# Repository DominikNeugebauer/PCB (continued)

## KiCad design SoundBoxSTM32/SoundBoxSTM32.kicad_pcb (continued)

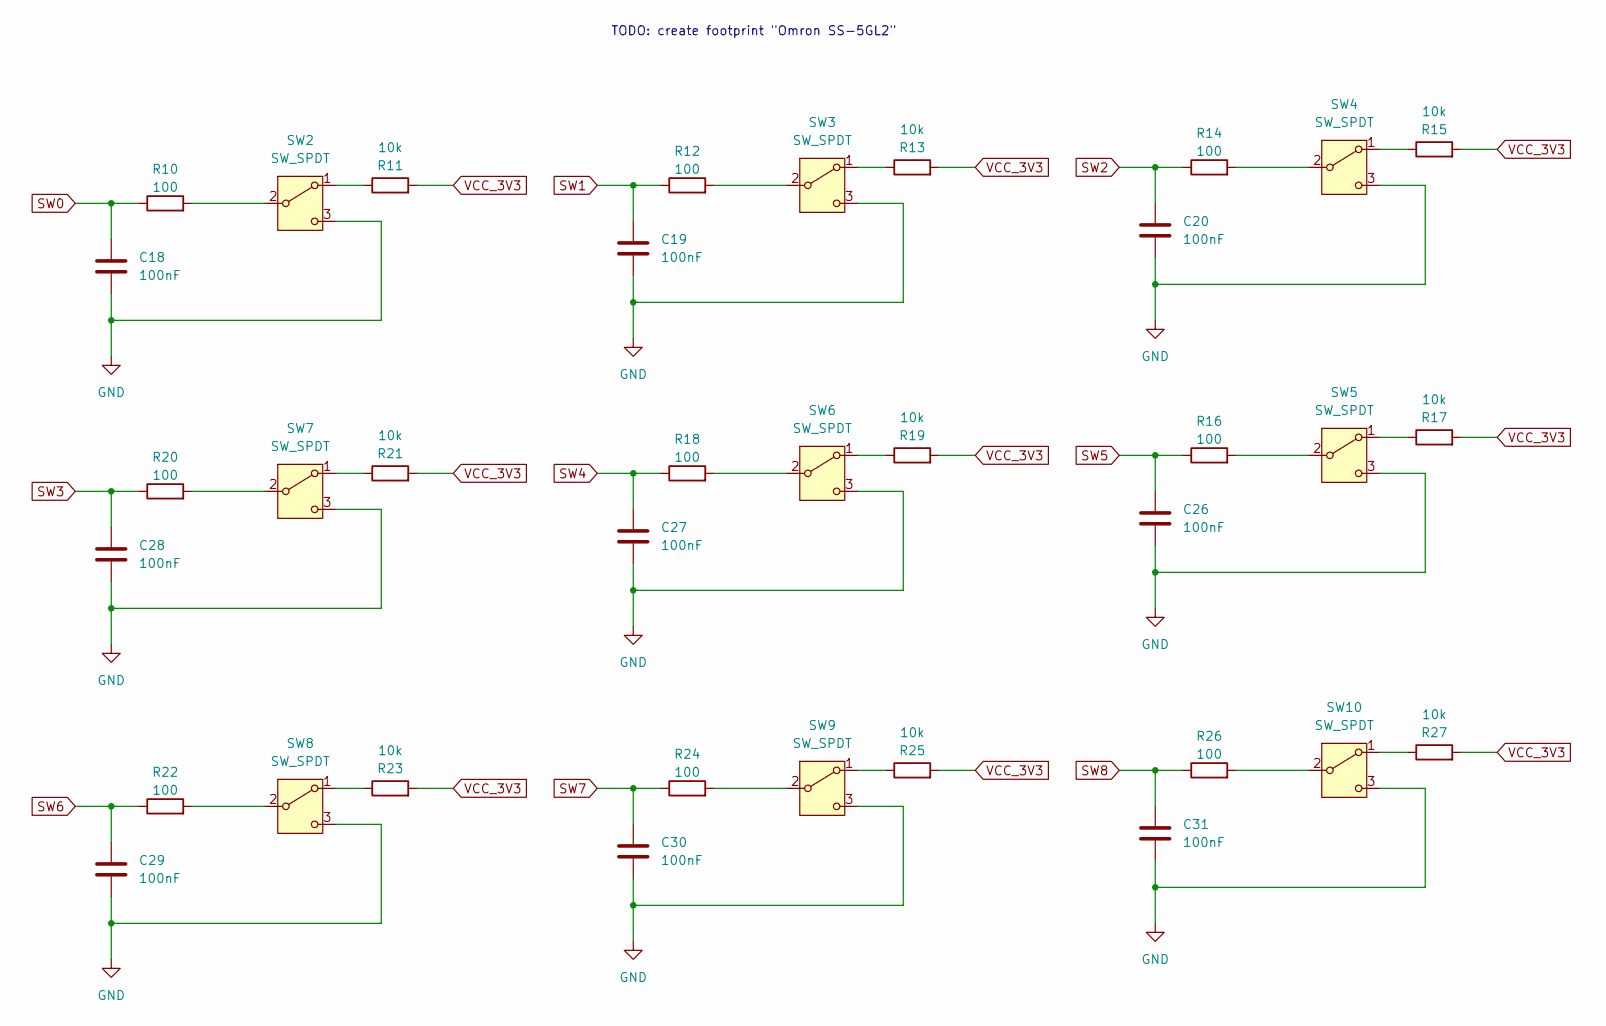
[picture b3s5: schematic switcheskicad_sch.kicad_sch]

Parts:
C18, C19, C20, C26, C27, C28, C29, C30, C31: 100nF; C_0603_1608Metric
R10, R12, R14, R16, R18, R20, R22, R24, R26: 100; R_0603_1608Metric
R11, R13, R15, R17, R19, R21, R23, R25, R27: 10k; R_0603_1608Metric
SW2, SW3, SW4, SW5, SW6, SW7, SW8, SW9, SW10: SW_SPDT; D2F-01L_OMR

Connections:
GND: C18.2, C19.2, C20.2, C26.2, C27.2, C28.2, C29.2, C30.2, C31.2, SW2.3 (C), SW3.3 (C), SW4.3 (C), SW5.3 (C), SW6.3 (C), SW7.3 (C), SW8.3 (C), SW9.3 (C), SW10.3 (C); also elsewhere on the board
unnamed: R11.1, SW2.1 (A)
unnamed: R10.2, SW2.2 (B)
unnamed: R13.1, SW3.1 (A)
unnamed: R12.2, SW3.2 (B)
unnamed: R15.1, SW4.1 (A)
unnamed: R14.2, SW4.2 (B)
unnamed: R17.1, SW5.1 (A)
unnamed: R16.2, SW5.2 (B)
unnamed: R19.1, SW6.1 (A)
unnamed: R18.2, SW6.2 (B)
unnamed: R21.1, SW7.1 (A)
unnamed: R20.2, SW7.2 (B)
unnamed: R23.1, SW8.1 (A)
unnamed: R22.2, SW8.2 (B)
unnamed: R25.1, SW9.1 (A)
unnamed: R24.2, SW9.2 (B)
unnamed: R27.1, SW10.1 (A)
unnamed: R26.2, SW10.2 (B)
SW0: C18.1, R10.1; also elsewhere on the board
SW1: C19.1, R12.1; also elsewhere on the board
SW2: C20.1, R14.1; also elsewhere on the board
SW3: C28.1, R20.1; also elsewhere on the board
SW4: C27.1, R18.1; also elsewhere on the board
SW5: C26.1, R16.1; also elsewhere on the board
SW6: C29.1, R22.1; also elsewhere on the board
SW7: C30.1, R24.1; also elsewhere on the board
SW8: C31.1, R26.1; also elsewhere on the board
VCC_3V3: R11.2, R13.2, R15.2, R17.2, R19.2, R21.2, R23.2, R25.2, R27.2; also elsewhere on the board

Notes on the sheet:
TODO: create footprint "Omron SS-5GL2"

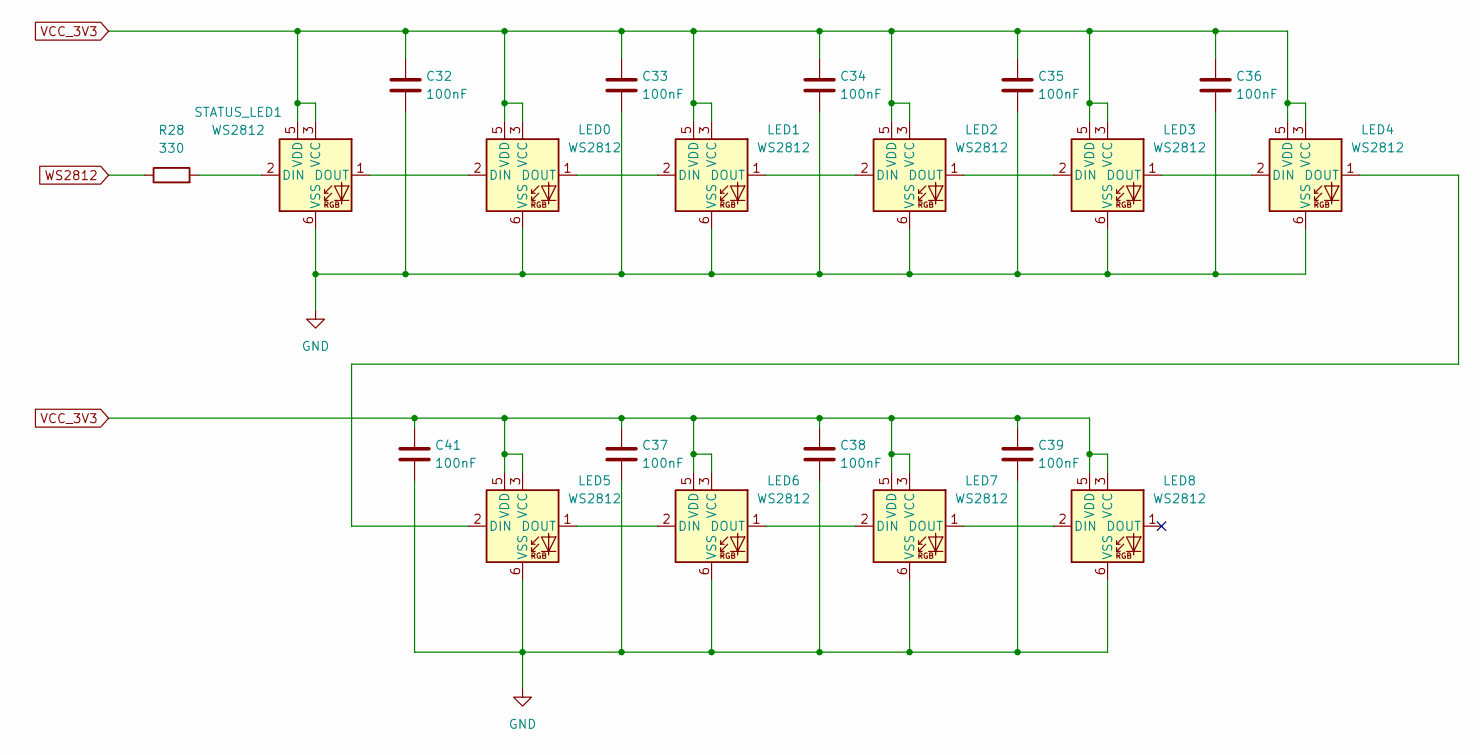
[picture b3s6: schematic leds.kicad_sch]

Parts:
C32, C33, C34, C35, C36, C37, C38, C39, C41: 100nF; C_0603_1608Metric
LED0, LED1, LED2, LED3, LED4, LED5, LED6, LED7, LED8: WS2812; LED_WS2812_PLCC6_5.0x5.0mm_P1.6mm
R28: 330; R_0603_1608Metric
STATUS_LED1: WS2812; LED_WS2812_PLCC6_5.0x5.0mm_P1.6mm

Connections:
GND: C32.2, C33.2, C34.2, C35.2, C36.2, C37.2, C38.2, C39.2, C41.2, LED0.6 (VSS), LED1.6 (VSS), LED2.6 (VSS), LED3.6 (VSS), LED4.6 (VSS), LED5.6 (VSS), LED6.6 (VSS), LED7.6 (VSS), LED8.6 (VSS), STATUS_LED1.6 (VSS); also elsewhere on the board
unnamed: LED0.2 (DIN), STATUS_LED1.1 (DOUT)
unnamed: LED0.1 (DOUT), LED1.2 (DIN)
unnamed: LED1.1 (DOUT), LED2.2 (DIN)
unnamed: LED2.1 (DOUT), LED3.2 (DIN)
unnamed: LED3.1 (DOUT), LED4.2 (DIN)
unnamed: LED4.1 (DOUT), LED5.2 (DIN)
unnamed: LED5.1 (DOUT), LED6.2 (DIN)
unnamed: LED6.1 (DOUT), LED7.2 (DIN)
unnamed: LED7.1 (DOUT), LED8.2 (DIN)
unnamed: R28.2, STATUS_LED1.2 (DIN)
VCC_3V3: C32.1, C33.1, C34.1, C35.1, C36.1, C37.1, C38.1, C39.1, C41.1, LED0.3 (VCC), LED0.5 (VDD), LED1.3 (VCC), LED1.5 (VDD), LED2.3 (VCC), LED2.5 (VDD), LED3.3 (VCC), LED3.5 (VDD), LED4.3 (VCC), LED4.5 (VDD), LED5.3 (VCC), LED5.5 (VDD), LED6.3 (VCC), LED6.5 (VDD), LED7.3 (VCC), LED7.5 (VDD), LED8.3 (VCC), LED8.5 (VDD), STATUS_LED1.3 (VCC), STATUS_LED1.5 (VDD); also elsewhere on the board
WS2812: R28.1; also elsewhere on the board

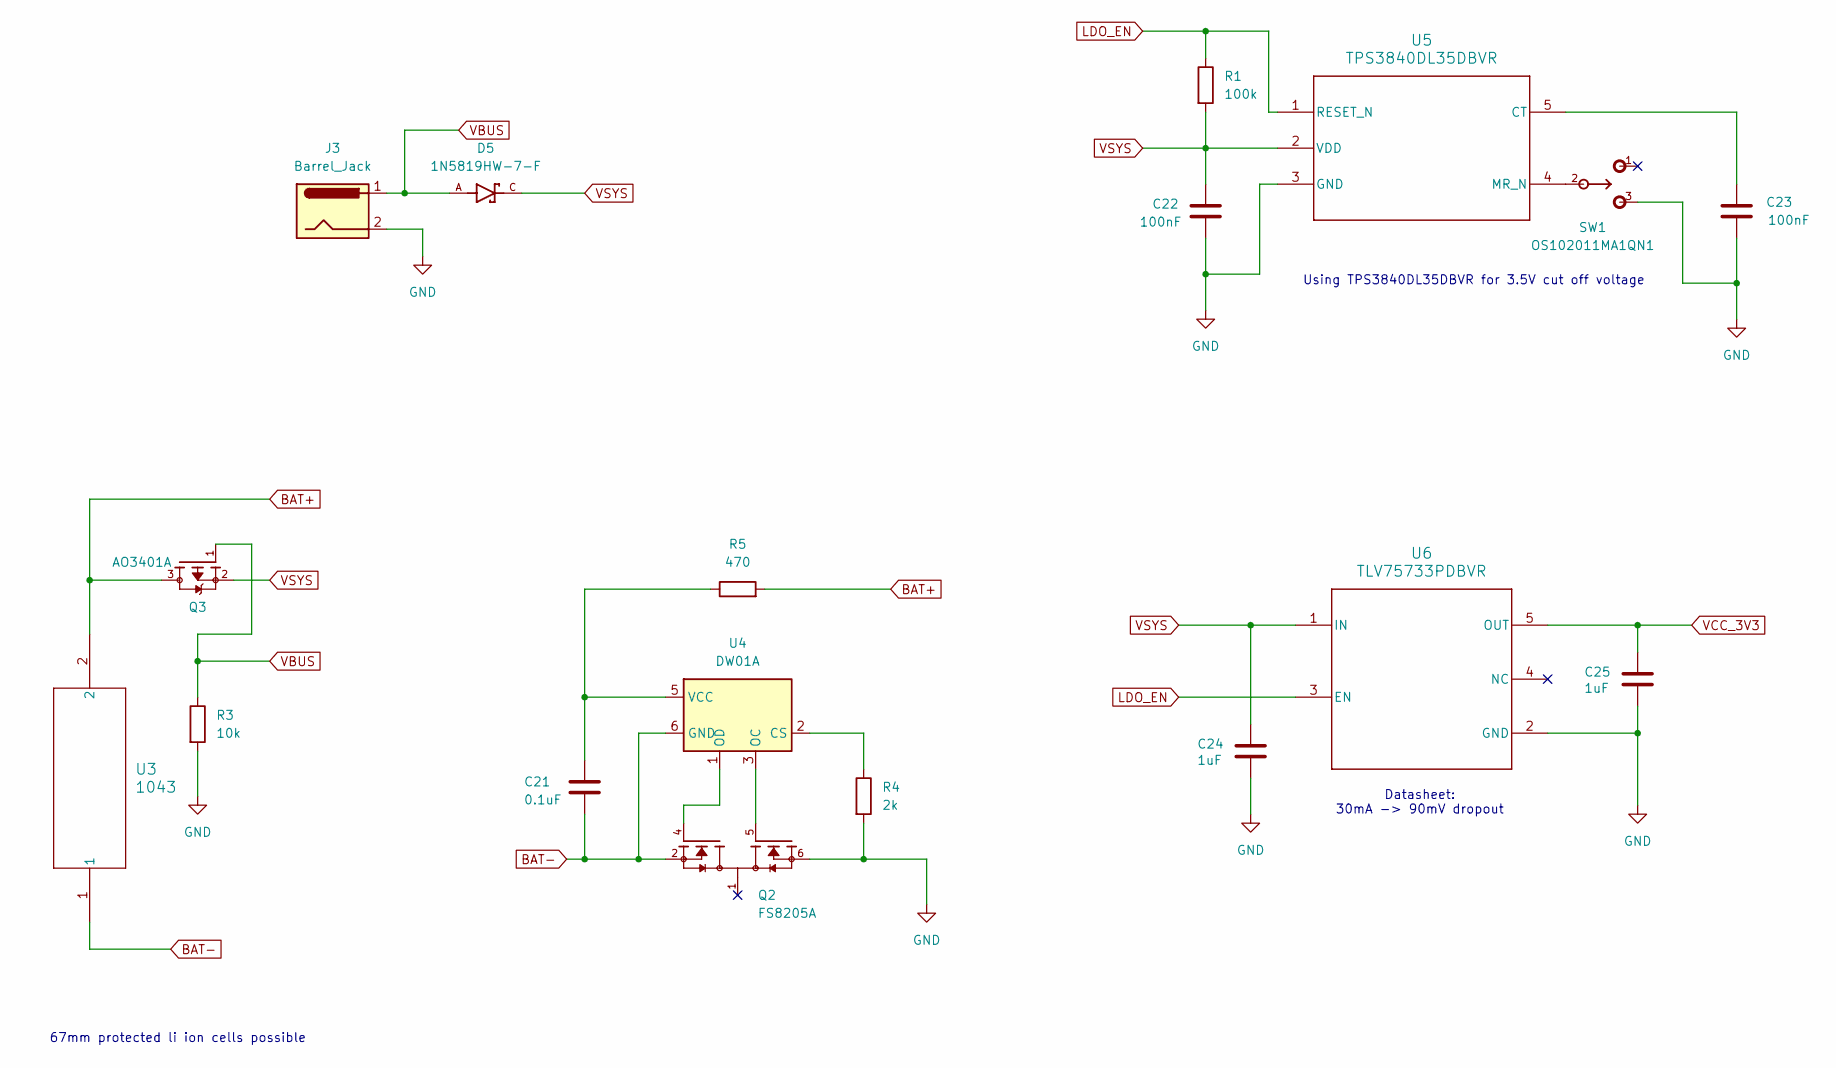
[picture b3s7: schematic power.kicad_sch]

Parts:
C21: 0.1uF; C_0603_1608Metric
C22, C23: 100nF; C_0603_1608Metric
C24, C25: 1uF; C_0603_1608Metric
D5: 1N5819HW-7-F; PARTREV 18-2
J3: Barrel_Jack; BarrelJack_Horizontal
Q2: FS8205A; PARTREV 1.7
Q3: AO3401A; PMOS-SOT23-3
R1: 100k; R_0603_1608Metric
R3: 10k; R_0603_1608Metric
R4: 2k; R_0603_1608Metric
R5: 470; R_0603_1608Metric
SW1: OS102011MA1QN1; MANUFACTURER_PART_NUMBER OS102011MA1QN1
U3: 1043; 1043_KEY
U4: DW01A; SOT-23-6
U5: TPS3840DL35DBVR; SOT-23-5
U6: TLV75733PDBVR; SOT95P280X145-5N_TLV75733PDBVR

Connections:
BAT+: Q3.3, R5.2, U3.2; also elsewhere on the board
BAT-: C21.2, Q2.2, Q2.3, U3.1, U4.6 (GND); also elsewhere on the board
GND: C22.2, C23.2, C24.2, C25.2, J3.2, Q2.6, Q2.7, R3.2, R4.2, SW1.3, U5.3 (GND), U6.2 (GND); also elsewhere on the board
LDO_EN: R1.1, U5.1 (RESET_N), U6.3 (EN)
unnamed: R4.1, U4.2 (CS)
unnamed: Q2.5, U4.3 (OC)
unnamed: Q2.4, U4.1 (OD)
unnamed: C21.1, R5.1, U4.5 (VCC)
unnamed: C23.1, U5.5 (CT)
unnamed: SW1.2, U5.4 (MR_N)
VBUS: D5.A, J3.1, Q3.1, R3.1
VCC_3V3: C25.1, U6.5 (OUT); also elsewhere on the board
VSYS: C22.1, C24.1, D5.C, Q3.2, R1.2, U5.2 (VDD), U6.1 (IN); also elsewhere on the board

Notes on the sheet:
Datasheet: 30mA -> 90mV dropout
67mm protected li ion cells possible
Using TPS3840DL35DBVR for 3.5V cut off voltage

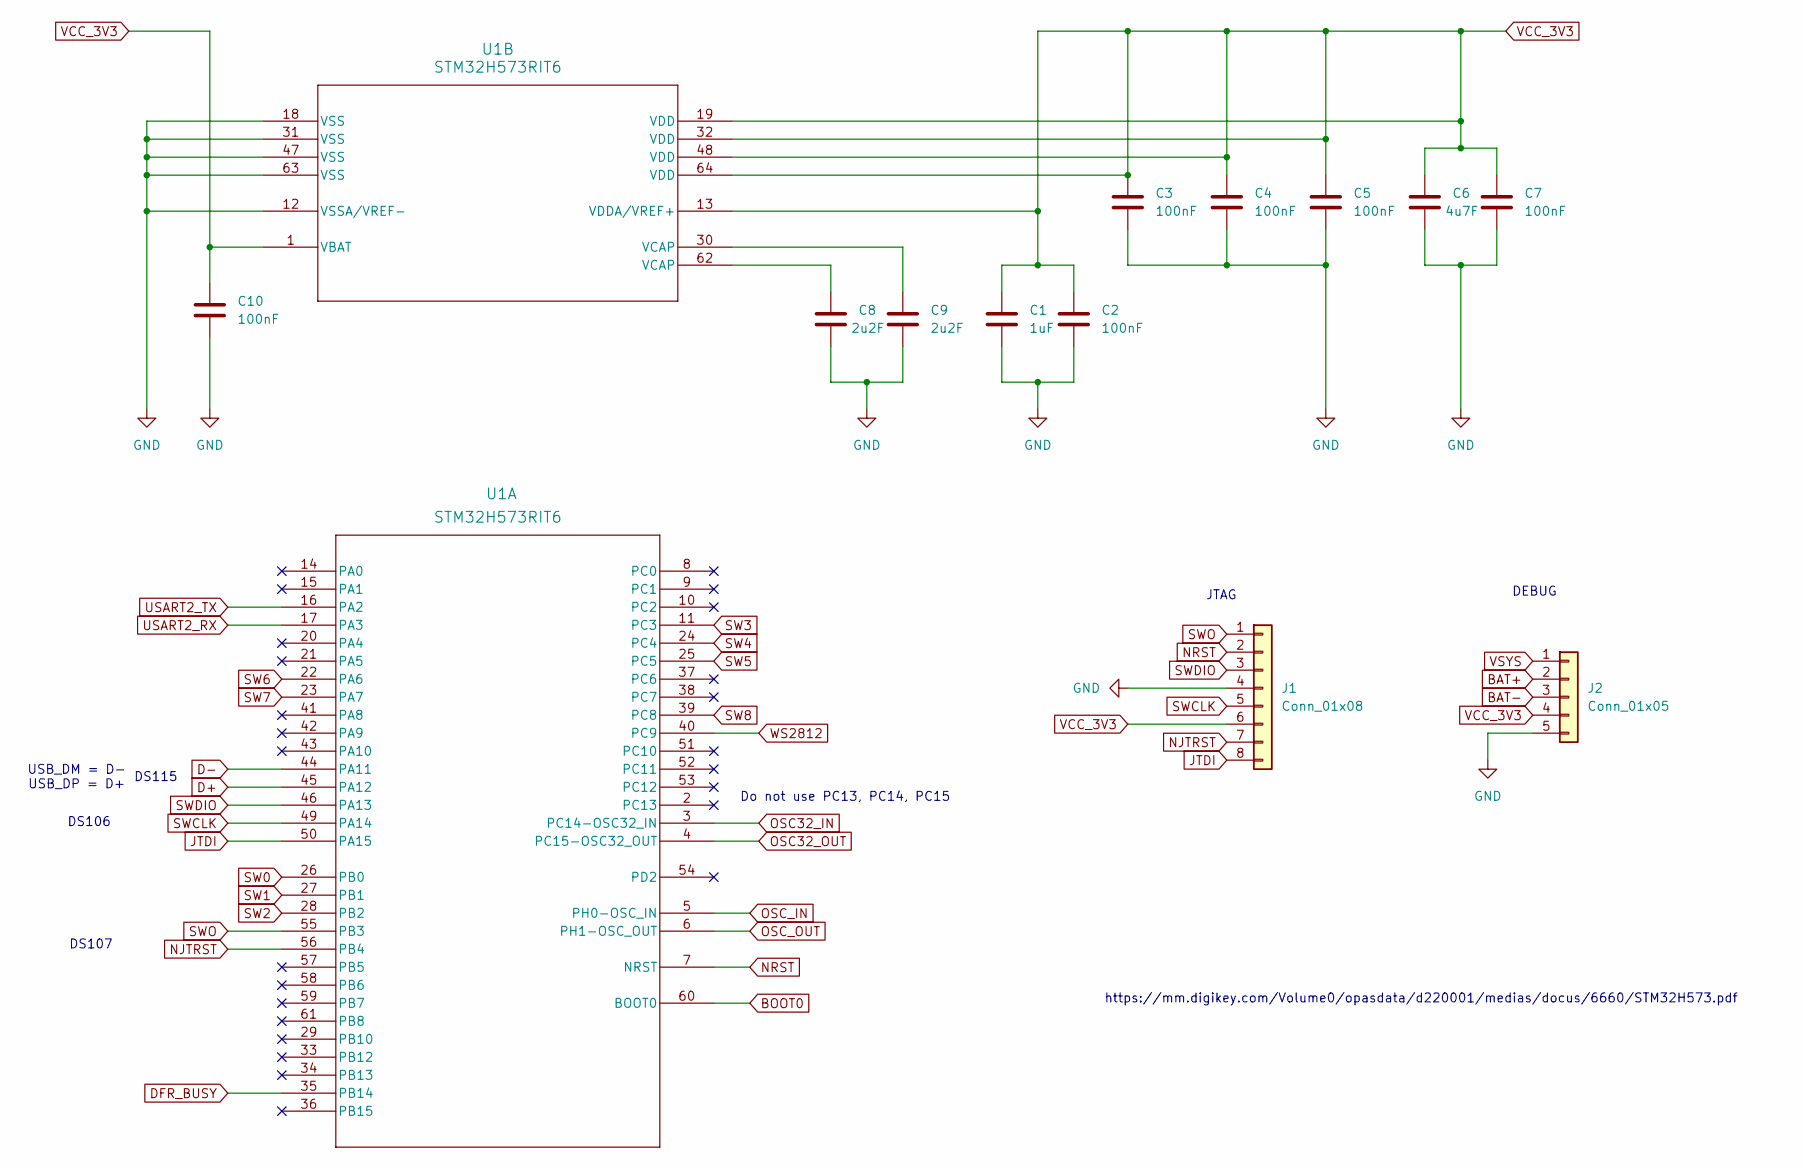
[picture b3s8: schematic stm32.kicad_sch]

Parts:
C1: 1uF; C_0603_1608Metric
C2, C3, C4, C5, C7, C10: 100nF; C_0603_1608Metric
C6: 4u7F; C_0603_1608Metric
C8, C9: 2u2F; C_0603_1608Metric
J1: Conn_01x08; PinHeader_1x08_P2.54mm_Vertical
J2: Conn_01x05; PinHeader_1x05_P2.54mm_Vertical
U1: STM32H573RIT6

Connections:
BAT+: J2.2; also elsewhere on the board
BAT-: J2.3; also elsewhere on the board
BOOT0: U1.60 (BOOT0); also elsewhere on the board
D+: U1.45 (PA12)
D-: U1.44 (PA11)
DFR_BUSY: U1.35 (PB14); also elsewhere on the board
GND: C1.2, C2.2, C3.2, C4.2, C5.2, C6.2, C7.2, C8.2, C9.2, C10.2, J1.4, J2.5, U1.12 (VSSA/VREF-), U1.18 (VSS), U1.31 (VSS), U1.47 (VSS), U1.63 (VSS); also elsewhere on the board
JTDI: J1.8, U1.50 (PA15)
NJTRST: J1.7, U1.56 (PB4)
NRST: J1.2, U1.7 (NRST); also elsewhere on the board
unnamed: C8.1, U1.62 (VCAP)
unnamed: C9.1, U1.30 (VCAP)
OSC32_IN: U1.3 (PC14-OSC32_IN); also elsewhere on the board
OSC32_OUT: U1.4 (PC15-OSC32_OUT); also elsewhere on the board
OSC_IN: U1.5 (PH0-OSC_IN); also elsewhere on the board
OSC_OUT: U1.6 (PH1-OSC_OUT); also elsewhere on the board
SW0: U1.26 (PB0); also elsewhere on the board
SW1: U1.27 (PB1); also elsewhere on the board
SW2: U1.28 (PB2); also elsewhere on the board
SW3: U1.11 (PC3); also elsewhere on the board
SW4: U1.24 (PC4); also elsewhere on the board
SW5: U1.25 (PC5); also elsewhere on the board
SW6: U1.22 (PA6); also elsewhere on the board
SW7: U1.23 (PA7); also elsewhere on the board
SW8: U1.39 (PC8); also elsewhere on the board
SWCLK: J1.5, U1.49 (PA14)
SWDIO: J1.3, U1.46 (PA13)
SWO: J1.1, U1.55 (PB3)
USART2_RX: U1.17 (PA3); also elsewhere on the board
USART2_TX: U1.16 (PA2); also elsewhere on the board
VCC_3V3: C1.1, C2.1, C3.1, C4.1, C5.1, C6.1, C7.1, C10.1, J1.6, J2.4, U1.1 (VBAT), U1.13 (VDDA/VREF+), U1.19 (VDD), U1.32 (VDD), U1.48 (VDD), U1.64 (VDD); also elsewhere on the board
VSYS: J2.1; also elsewhere on the board
WS2812: U1.40 (PC9); also elsewhere on the board

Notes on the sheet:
JTAG
DS106
https://mm.digikey.com/Volume0/opasdata/d220001/medias/docus/6660/STM32H573.pdf
DEBUG
Do not use PC13, PC14, PC15
DS115
DS107
USB_DM = D- USB_DP = D+

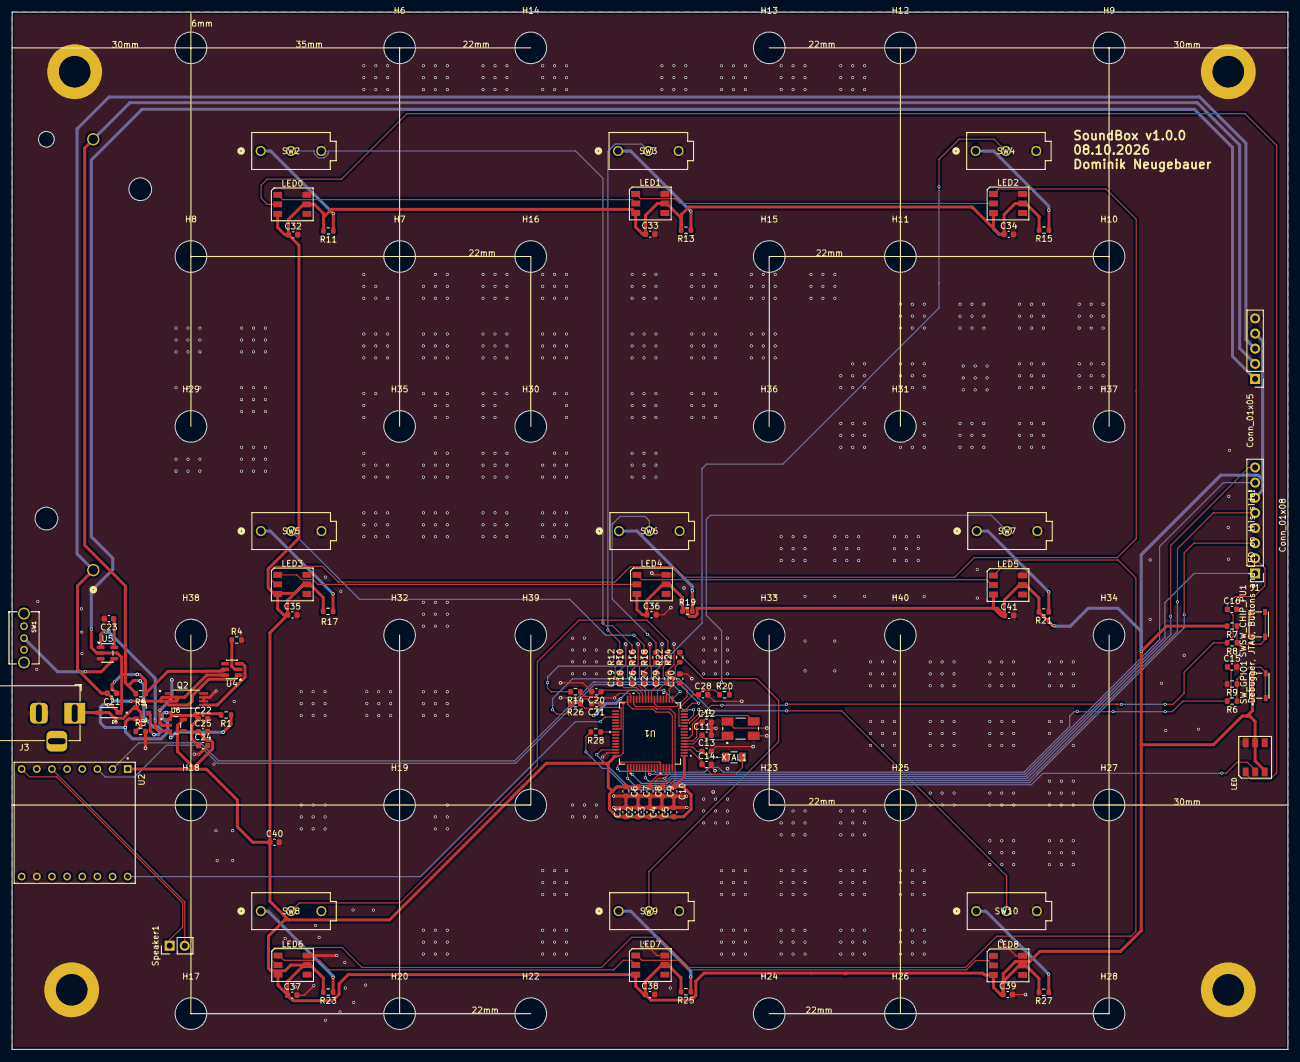
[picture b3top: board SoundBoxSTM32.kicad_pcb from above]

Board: 2 copper layers, 214.0 x 174.0 mm, 144 parts (1 on the bottom side), 71 nets.

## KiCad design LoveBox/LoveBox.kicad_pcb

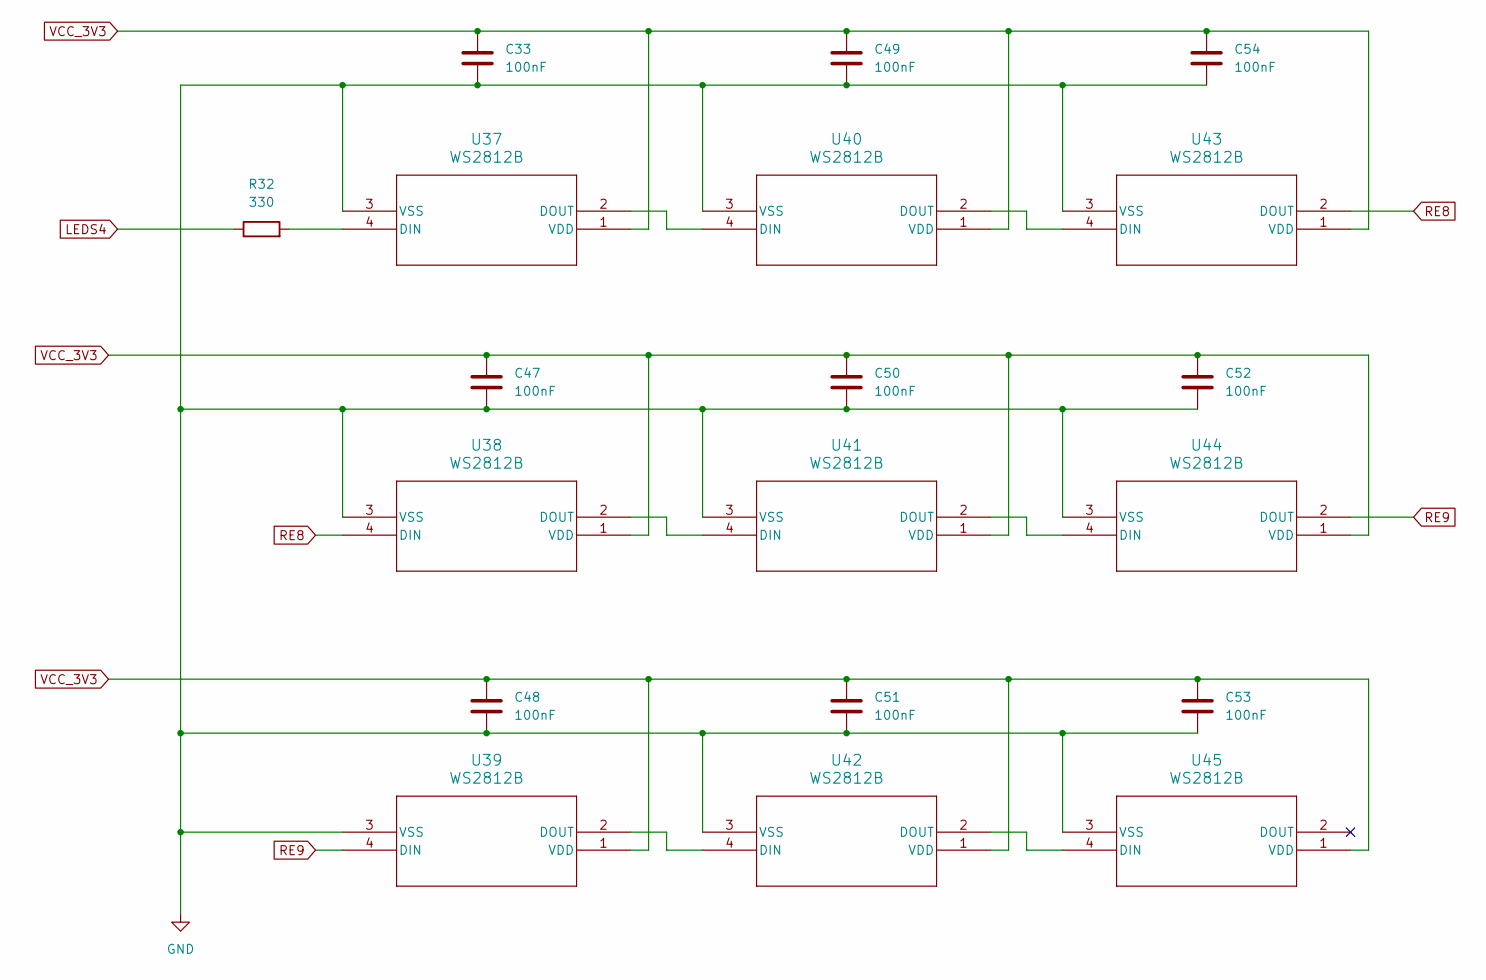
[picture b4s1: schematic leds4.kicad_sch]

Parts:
C33, C47, C48, C49, C50, C51, C52, C53, C54: 100nF; C_0603_1608Metric
R32: 330; R_0603_1608Metric
U37, U38, U39, U40, U41, U42, U43, U44, U45: WS2812B; WS2812B_WDS

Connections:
GND: C33.2, C47.2, C48.2, C49.2, C50.2, C51.2, C52.2, C53.2, C54.2, U37.3 (VSS), U38.3 (VSS), U39.3 (VSS), U40.3 (VSS), U41.3 (VSS), U42.3 (VSS), U43.3 (VSS), U44.3 (VSS), U45.3 (VSS); also elsewhere on the board
LEDS4: R32.1; also elsewhere on the board
unnamed: R32.2, U37.4 (DIN)
unnamed: U37.2 (DOUT), U40.4 (DIN)
unnamed: U38.2 (DOUT), U41.4 (DIN)
unnamed: U39.2 (DOUT), U42.4 (DIN)
unnamed: U40.2 (DOUT), U43.4 (DIN)
unnamed: U41.2 (DOUT), U44.4 (DIN)
unnamed: U42.2 (DOUT), U45.4 (DIN)
RE8: U38.4 (DIN), U43.2 (DOUT)
RE9: U39.4 (DIN), U44.2 (DOUT)
VCC_3V3: C33.1, C47.1, C48.1, C49.1, C50.1, C51.1, C52.1, C53.1, C54.1, U37.1 (VDD), U38.1 (VDD), U39.1 (VDD), U40.1 (VDD), U41.1 (VDD), U42.1 (VDD), U43.1 (VDD), U44.1 (VDD), U45.1 (VDD); also elsewhere on the board

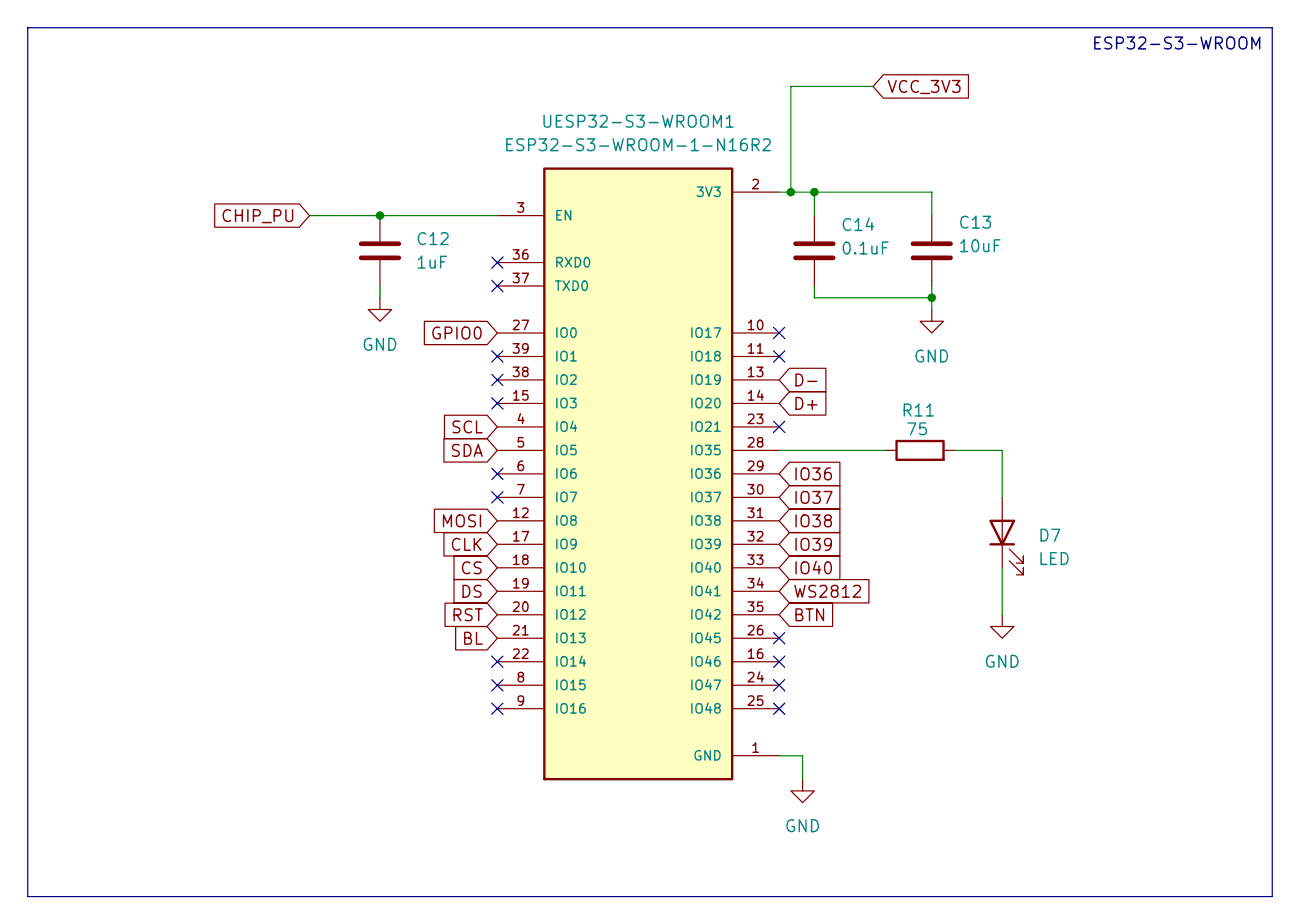
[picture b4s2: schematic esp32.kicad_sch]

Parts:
C12: 1uF; C_0603_1608Metric
C13: 10uF; C_0603_1608Metric
C14: 0.1uF; C_0603_1608Metric
D7: LED; LED_1206_3216Metric
R11: 75; R_0603_1608Metric
UESP32-S3-WROOM1: ESP32-S3-WROOM-1-N16R2; PARTREV v1.0

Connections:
BL: UESP32-S3-WROOM1.21 (IO13)
BTN: UESP32-S3-WROOM1.35 (IO42); also elsewhere on the board
CHIP_PU: C12.1, UESP32-S3-WROOM1.3 (EN); also elsewhere on the board
CLK: UESP32-S3-WROOM1.17 (IO9)
CS: UESP32-S3-WROOM1.18 (IO10)
D+: UESP32-S3-WROOM1.14 (IO20); also elsewhere on the board
D-: UESP32-S3-WROOM1.13 (IO19); also elsewhere on the board
DS: UESP32-S3-WROOM1.19 (IO11)
GND: C12.2, C13.2, C14.2, D7.1 (K), UESP32-S3-WROOM1.1 (GND), UESP32-S3-WROOM1.40 (GND), UESP32-S3-WROOM1.41_1 (GND), UESP32-S3-WROOM1.41_2 (GND), UESP32-S3-WROOM1.41_3 (GND), UESP32-S3-WROOM1.41_4 (GND), UESP32-S3-WROOM1.41_5 (GND), UESP32-S3-WROOM1.41_6 (GND), UESP32-S3-WROOM1.41_7 (GND), UESP32-S3-WROOM1.41_8 (GND), UESP32-S3-WROOM1.41_9 (GND), UESP32-S3-WROOM1.41_10, UESP32-S3-WROOM1.41_11, UESP32-S3-WROOM1.41_12, UESP32-S3-WROOM1.41_13, UESP32-S3-WROOM1.41_14, UESP32-S3-WROOM1.41_15, UESP32-S3-WROOM1.41_16, UESP32-S3-WROOM1.41_17, UESP32-S3-WROOM1.41_18, UESP32-S3-WROOM1.41_19, UESP32-S3-WROOM1.41_20, UESP32-S3-WROOM1.41_21; also elsewhere on the board
GPIO0: UESP32-S3-WROOM1.27 (IO0); also elsewhere on the board
IO36: UESP32-S3-WROOM1.29 (IO36)
IO37: UESP32-S3-WROOM1.30 (IO37)
IO38: UESP32-S3-WROOM1.31 (IO38)
IO39: UESP32-S3-WROOM1.32 (IO39)
IO40: UESP32-S3-WROOM1.33 (IO40)
MOSI: UESP32-S3-WROOM1.12 (IO8)
unnamed: D7.2 (A), R11.2
unnamed: R11.1, UESP32-S3-WROOM1.28 (IO35)
RST: UESP32-S3-WROOM1.20 (IO12)
SCL: UESP32-S3-WROOM1.4 (IO4)
SDA: UESP32-S3-WROOM1.5 (IO5)
VCC_3V3: C13.1, C14.1, UESP32-S3-WROOM1.2 (3V3); also elsewhere on the board
WS2812: UESP32-S3-WROOM1.34 (IO41); also elsewhere on the board

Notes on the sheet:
ESP32-S3-WROOM

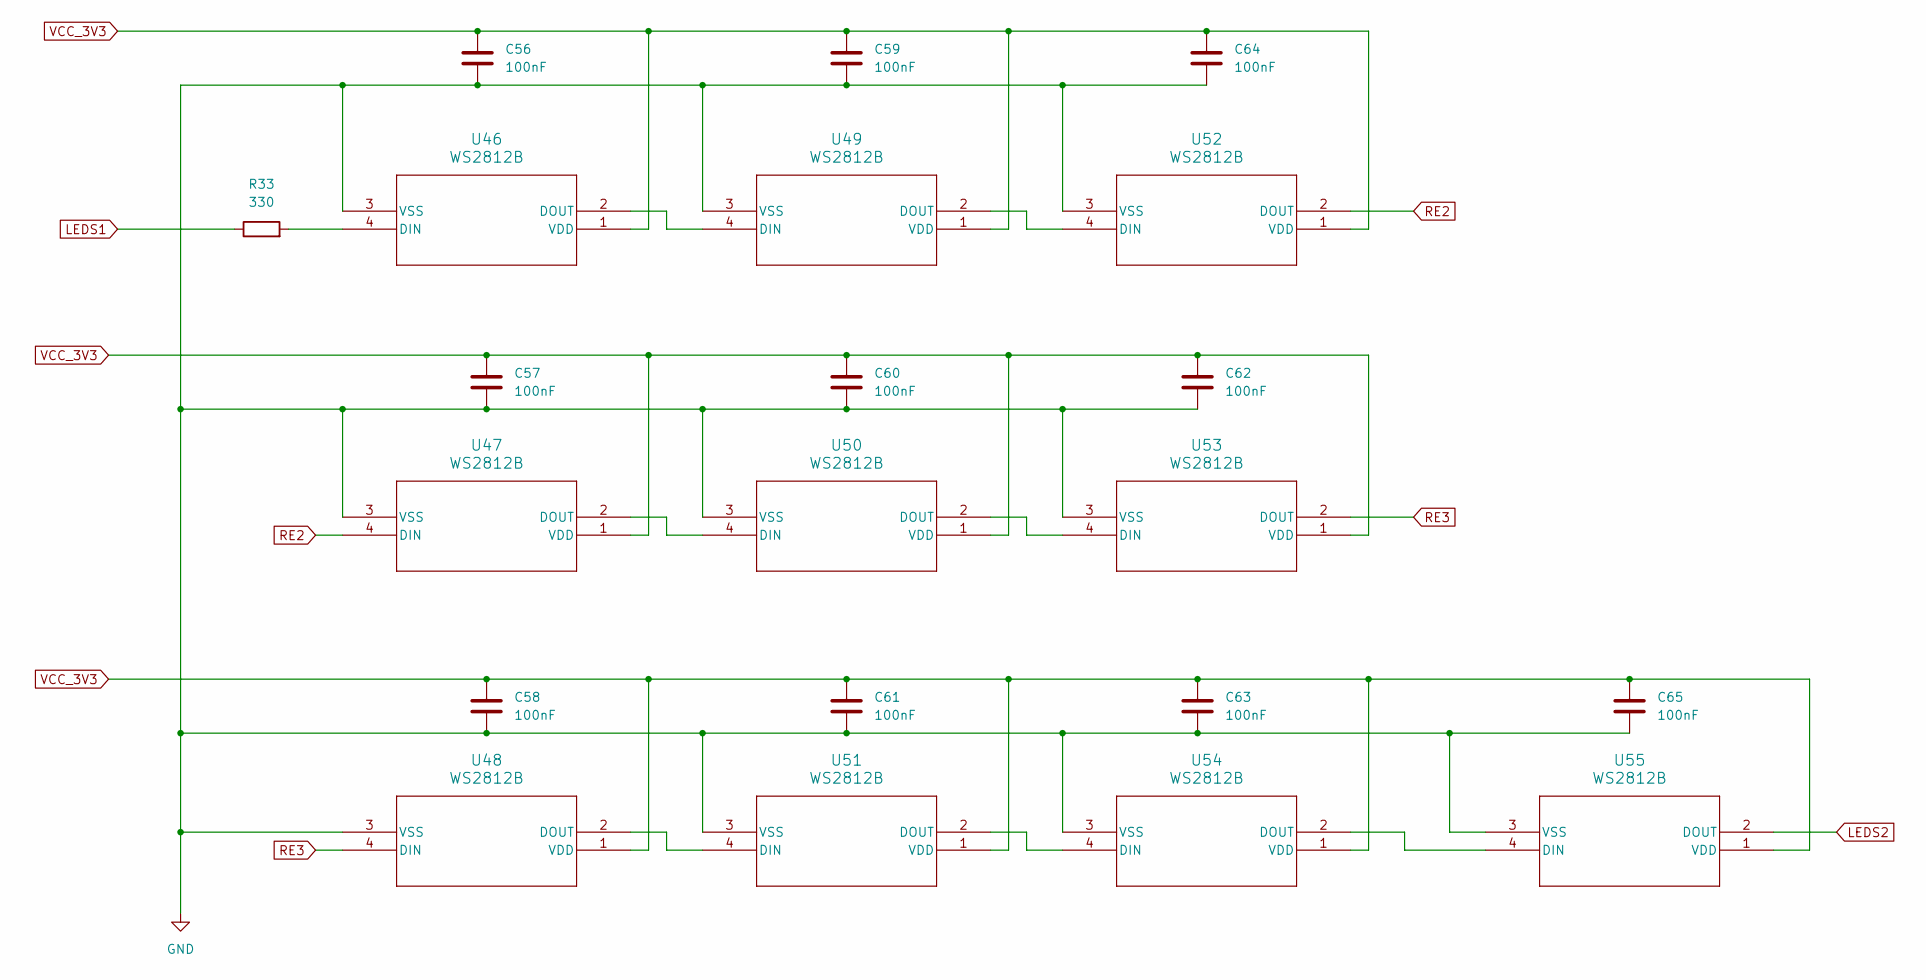
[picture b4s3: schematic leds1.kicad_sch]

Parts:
C56, C57, C58, C59, C60, C61, C62, C63, C64, C65: 100nF; C_0603_1608Metric
R33: 330; R_0603_1608Metric
U46, U47, U48, U49, U50, U51, U52, U53, U54, U55: WS2812B; WS2812B_WDS

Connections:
GND: C56.2, C57.2, C58.2, C59.2, C60.2, C61.2, C62.2, C63.2, C64.2, C65.2, U46.3 (VSS), U47.3 (VSS), U48.3 (VSS), U49.3 (VSS), U50.3 (VSS), U51.3 (VSS), U52.3 (VSS), U53.3 (VSS), U54.3 (VSS), U55.3 (VSS); also elsewhere on the board
LEDS1: R33.1; also elsewhere on the board
LEDS2: U55.2 (DOUT); also elsewhere on the board
unnamed: R33.2, U46.4 (DIN)
unnamed: U46.2 (DOUT), U49.4 (DIN)
unnamed: U47.2 (DOUT), U50.4 (DIN)
unnamed: U48.2 (DOUT), U51.4 (DIN)
unnamed: U49.2 (DOUT), U52.4 (DIN)
unnamed: U50.2 (DOUT), U53.4 (DIN)
unnamed: U51.2 (DOUT), U54.4 (DIN)
unnamed: U54.2 (DOUT), U55.4 (DIN)
RE2: U47.4 (DIN), U52.2 (DOUT)
RE3: U48.4 (DIN), U53.2 (DOUT)
VCC_3V3: C56.1, C57.1, C58.1, C59.1, C60.1, C61.1, C62.1, C63.1, C64.1, C65.1, U46.1 (VDD), U47.1 (VDD), U48.1 (VDD), U49.1 (VDD), U50.1 (VDD), U51.1 (VDD), U52.1 (VDD), U53.1 (VDD), U54.1 (VDD), U55.1 (VDD); also elsewhere on the board

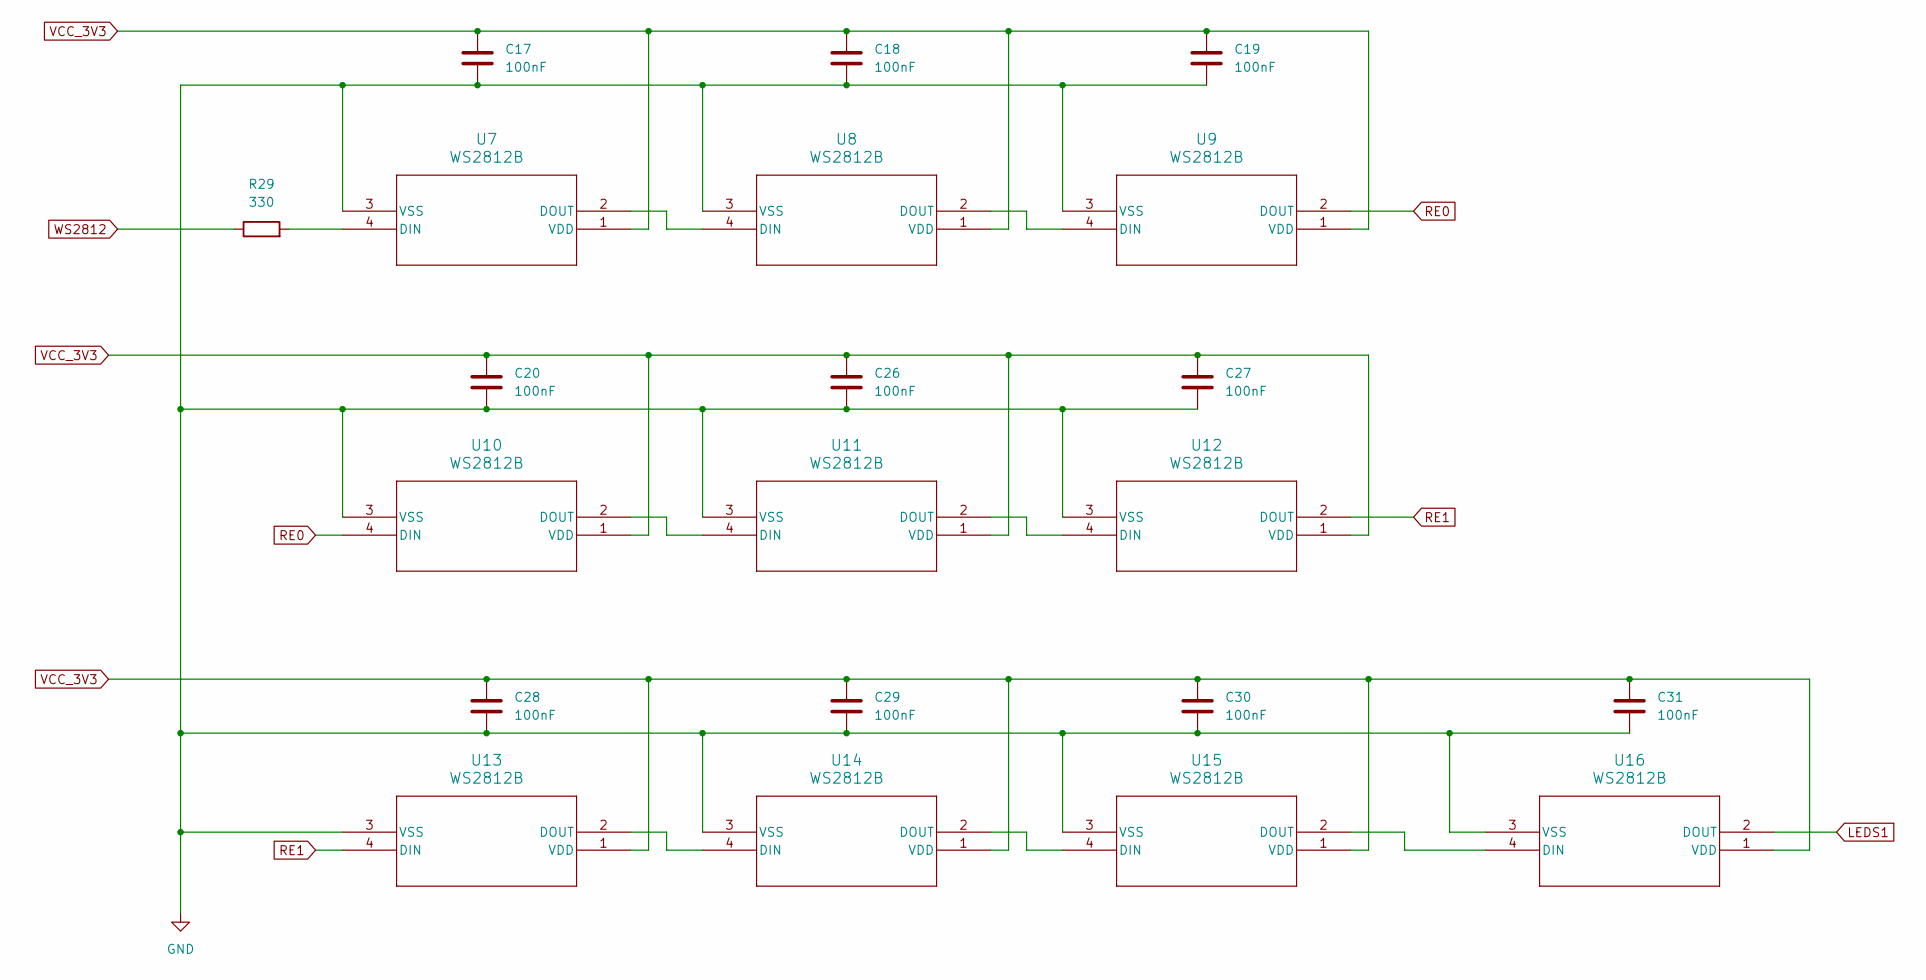
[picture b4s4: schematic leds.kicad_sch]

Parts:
C17, C18, C19, C20, C26, C27, C28, C29, C30, C31: 100nF; C_0603_1608Metric
R29: 330; R_0603_1608Metric
U7, U8, U9, U10, U11, U12, U13, U14, U15, U16: WS2812B; WS2812B_WDS

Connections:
GND: C17.2, C18.2, C19.2, C20.2, C26.2, C27.2, C28.2, C29.2, C30.2, C31.2, U7.3 (VSS), U8.3 (VSS), U9.3 (VSS), U10.3 (VSS), U11.3 (VSS), U12.3 (VSS), U13.3 (VSS), U14.3 (VSS), U15.3 (VSS), U16.3 (VSS); also elsewhere on the board
LEDS1: U16.2 (DOUT); also elsewhere on the board
unnamed: R29.2, U7.4 (DIN)
unnamed: U7.2 (DOUT), U8.4 (DIN)
unnamed: U8.2 (DOUT), U9.4 (DIN)
unnamed: U10.2 (DOUT), U11.4 (DIN)
unnamed: U11.2 (DOUT), U12.4 (DIN)
unnamed: U13.2 (DOUT), U14.4 (DIN)
unnamed: U14.2 (DOUT), U15.4 (DIN)
unnamed: U15.2 (DOUT), U16.4 (DIN)
RE0: U9.2 (DOUT), U10.4 (DIN)
RE1: U12.2 (DOUT), U13.4 (DIN)
VCC_3V3: C17.1, C18.1, C19.1, C20.1, C26.1, C27.1, C28.1, C29.1, C30.1, C31.1, U7.1 (VDD), U8.1 (VDD), U9.1 (VDD), U10.1 (VDD), U11.1 (VDD), U12.1 (VDD), U13.1 (VDD), U14.1 (VDD), U15.1 (VDD), U16.1 (VDD); also elsewhere on the board
WS2812: R29.1; also elsewhere on the board

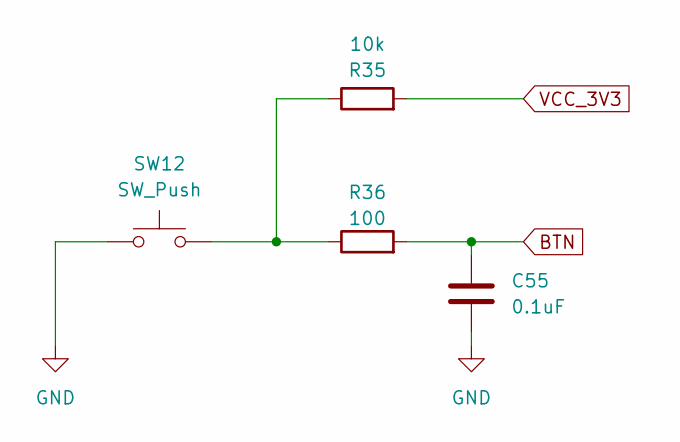
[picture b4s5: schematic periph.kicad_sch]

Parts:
C55: 0.1uF; C_0603_1608Metric
R35: 10k; R_0603_1608Metric
R36: 100; R_0603_1608Metric
SW12: SW_Push; SW_Cherry_MX_1.00u_PCB

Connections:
BTN: C55.1, R36.2; also elsewhere on the board
GND: C55.2, SW12.1; also elsewhere on the board
unnamed: R35.1, R36.1, SW12.2
VCC_3V3: R35.2; also elsewhere on the board
